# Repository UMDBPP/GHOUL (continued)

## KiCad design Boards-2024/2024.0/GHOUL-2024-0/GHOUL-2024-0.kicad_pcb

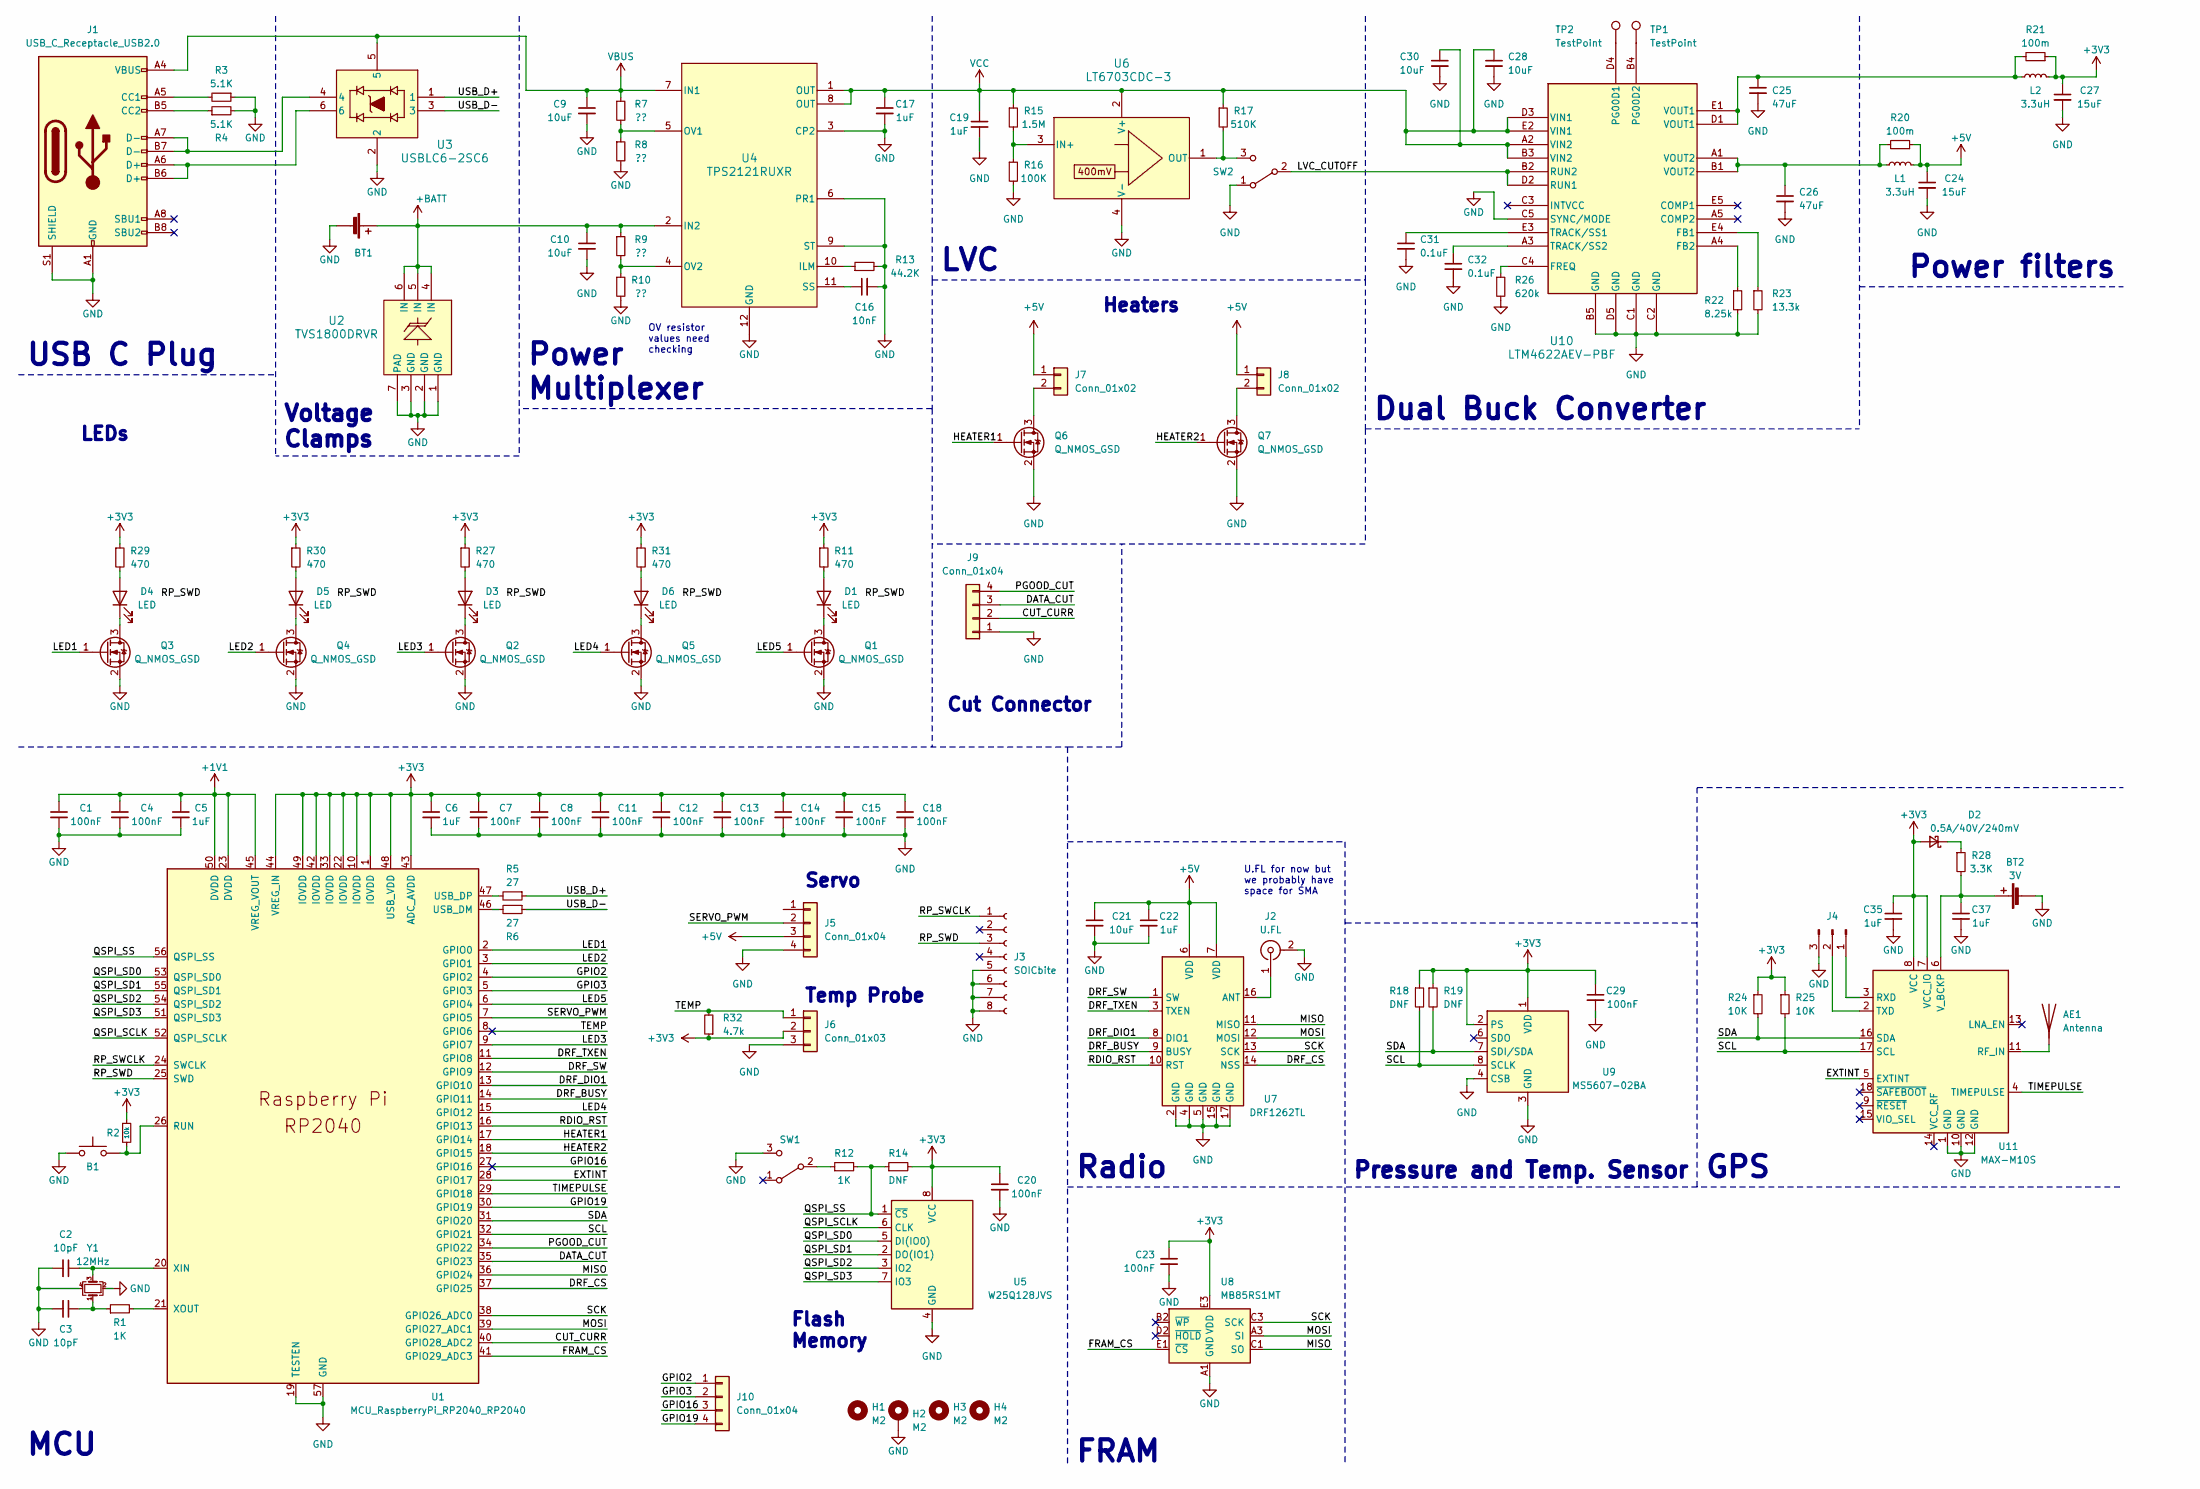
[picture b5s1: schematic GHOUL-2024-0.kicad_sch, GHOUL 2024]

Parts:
AE1: Antenna; ANT_1575AT_JOT-M
B1: KMR2; SW_Push_1P1T_NO_CK_KMR2
BT1: 1S1P LiPo; AMASS_XT30PW-M_1x02_P2.50mm_Horizontal
BT2: 3V; SEIKO_ML414H_IV01E
C1, C4, C7, C8, C11, C12, C13, C14, C15, C18, C20: 100nF; C_0402_1005Metric
C2, C3: 10pF; C_0402_1005Metric
C5, C6, C19: 1uF; C_0402_1005Metric
C9, C10, C21, C28, C30: 10uF; C_0603_1608Metric
C16: 10nF; C_0603_1608Metric
C17, C22, C35, C37: 1uF; C_0603_1608Metric
C23, C29: 100nF; C_0603_1608Metric
C24, C27: 15uF; C_1206_3216Metric
C25, C26: 47uF; C_0805_2012Metric
C31, C32: 0.1uF; C_0603_1608Metric
D1, D3, D4, D5, D6: LED; LED_0603_1608Metric
D2: 0.5A/40V/240mV; D_SOD-123F
H1, H2, H3, H4: M2; MountingHole_2.2mm_M2_Pad
J1: USB_C_Receptacle_USB2.0; USB_C_Receptacle_GCT_USB4105-xx-A_16P_TopMnt_Horizontal
J2: U.FL; U.FL_Molex_MCRF_73412-0110_Vertical
J3: SOICbite; SOIC_clipProgSmall
J4: Conn_01x03_Pin; PinHeader_1x03_P2.54mm_Vertical
J5, J9: Conn_01x04; Molex_SL_171971-0004_1x04_P2.54mm_Vertical
J6: Conn_01x03; Molex_SL_171971-0003_1x03_P2.54mm_Vertical
J7, J8: Conn_01x02; Molex_SL_171971-0002_1x02_P2.54mm_Vertical
J10: Conn_01x04; PinHeader_1x04_P2.54mm_Vertical
L1, L2: 3.3uH; L_1210_3225Metric
Q1, Q2, Q3, Q4, Q5: Q_NMOS_GSD; SOT-23-3
Q6, Q7: Q_NMOS_GSD; SC-59
R1: 1K; C_0402_1005Metric
R2: 10k; R_0603_1608Metric
R3, R4: 5.1K; R_0603_1608Metric_Pad0.98x0.95mm_HandSolder
R5, R6: 27; R_0603_1608Metric
R7, R8, R9, R10: ??; R_0603_1608Metric
R11, R27, R29, R30, R31: 470; R_0603_1608Metric
R12: 1K; R_0603_1608Metric
R13: 44.2K; R_0603_1608Metric
R14, R18, R19: DNF; R_0603_1608Metric
R15: 1.5M; R_0603_1608Metric
R16: 100K; R_0603_1608Metric
R17: 510K; R_0603_1608Metric
R20, R21: 100m; R_0603_1608Metric
R22: 8.25k; R_0603_1608Metric
R23: 13.3k; R_0603_1608Metric
R24, R25: 10K; R_0603_1608Metric
R26: 620k; R_0603_1608Metric
R28: 3.3K; R_0603_1608Metric
R32: 4.7k; R_0603_1608Metric
SW1: CAS-120TB_NDC-M
SW2: SLIDE; CL-SB-12B-01_NDC
TP1, TP2: TestPoint; TestPoint_Keystone_5000-5004_Miniature
U1: MCU_RaspberryPi_RP2040_RP2040; RP2040-QFN-56
U2: TVS1800DRVR; TVS1800
U3: USBLC6-2SC6; SOT-23-6
U4: TPS2121RUXR; TPS2121
U5: W25Q128JVS; W25Q64JVZP
U6: LT6703CDC-3; DFN-3_DC_LIT
U7: DRF1262TL
U8: MB85RS1MT; BGA8CP30X40_5X3_309X228X35B25N
U9: MS5607-02BA; LGA-8_3x5mm_P1.25mm
U10: LTM4622AEV-PBF; LGA25_6P25X6P25_ADI
U11: MAX-M10S; ublox_MAX
Y1: 12MHz; Crystal_SMD_2520-4Pin_2.5x2.0mm

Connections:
+1V1: C1.1, C4.1, C5.1, U1.23 (DVDD), U1.45 (VREG_VOUT), U1.50 (DVDD)
+3V3: C6.1, C7.1, C8.1, C11.1, C12.1, C13.1, C14.1, C15.1, C18.1, C20.1, C23.1, C27.1, C29.1, C35.1, D2.2 (A), J6.2, L2.1, R2.1, R11.1, R14.2, R18.1, R19.1, R21.1, R24.1, R25.1, R27.1, R29.1, R30.1, R31.1, R32.1, U1.1 (IOVDD), U1.10 (IOVDD), U1.22 (IOVDD), U1.33 (IOVDD), U1.42 (IOVDD), U1.43 (ADC_AVDD), U1.44 (VREG_IN), U1.48 (USB_VDD), U1.49 (IOVDD), U5.8 (VCC), U8.E3 (VDD), U9.1 (VDD), U9.2 (PS), U11.7 (VCC_IO), U11.8 (VCC)
+5V: C21.1, C22.1, C24.1, J5.3, J7.1, J8.1, L1.1, R20.1, U7.6 (VDD), U7.7 (VDD)
+BATT: BT1.2 (+), C10.1, R9.1, U2.4 (IN), U2.5 (IN), U2.6 (IN), U4.2 (IN2)
/CUT_CURR: J9.2, U1.40 (GPIO28_ADC2)
/DATA_CUT: J9.3, U1.35 (GPIO23)
/DRF_BUSY: U1.14 (GPIO11), U7.9 (BUSY)
/DRF_CS: U1.37 (GPIO25), U7.14 (NSS)
/DRF_DIO1: U1.13 (GPIO10), U7.8 (DIO1)
/DRF_SW: U1.12 (GPIO9), U7.1 (SW)
/DRF_TXEN: U1.11 (GPIO8), U7.3 (TXEN)
/EXTINT: U1.28 (GPIO17), U11.5 (EXTINT)
/FRAM_CS: U1.41 (GPIO29_ADC3), U8.E1 (~CS)
/GPIO2: J10.1, U1.4 (GPIO2)
/GPIO3: J10.2, U1.5 (GPIO3)
/GPIO16: J10.3, U1.27 (GPIO16)
/GPIO19: J10.4, U1.30 (GPIO19)
/HEATER1: Q6.1 (G), U1.17 (GPIO14)
/HEATER2: Q7.1 (G), U1.18 (GPIO15)
/LED1: Q3.1 (G), U1.2 (GPIO0)
/LED2: Q4.1 (G), U1.3 (GPIO1)
/LED3: Q2.1 (G), U1.9 (GPIO7)
/LED4: Q5.1 (G), U1.15 (GPIO12)
/LED5: Q1.1 (G), U1.6 (GPIO4)
/LVC_CUTOFF: SW2.2 (B), U10.B2 (RUN2), U10.D2 (RUN1)
/MISO: U1.36 (GPIO24), U7.11 (MISO), U8.C1 (SO)
/MOSI: U1.39 (GPIO27_ADC1), U7.12 (MOSI), U8.A3 (SI)
/PGOOD_CUT: J9.4, U1.34 (GPIO22)
/QSPI_SCLK: U1.52 (QSPI_SCLK), U5.6 (CLK)
/QSPI_SD0: U1.53 (QSPI_SD0), U5.5 (DI(IO0))
/QSPI_SD1: U1.55 (QSPI_SD1), U5.2 (DO(IO1))
/QSPI_SD2: U1.54 (QSPI_SD2), U5.3 (IO2)
/QSPI_SD3: U1.51 (QSPI_SD3), U5.7 (IO3)
/QSPI_SS: R12.2, R14.1, U1.56 (QSPI_SS), U5.1 (~CS)
/RDIO_RST: U1.16 (GPIO13), U7.10 (RST)
/RP_SWCLK: J3.1, U1.24 (SWCLK)
/RP_SWD: J3.3, U1.25 (SWD)
/SCK: U1.38 (GPIO26_ADC0), U7.13 (SCK), U8.C3 (SCK)
/SCL: R18.2, R25.2, U1.32 (GPIO21), U9.8 (SCLK), U11.17 (SCL)
/SDA: R19.2, R24.2, U1.31 (GPIO20), U9.7 (SDI/SDA), U11.16 (SDA)
/SERVO_PWM: J5.2, U1.7 (GPIO5)
/TEMP: J6.1, R32.2, U1.8 (GPIO6)
/TIMEPULSE: U1.29 (GPIO18), U11.4 (TIMEPULSE)
/USB_D+: R5.1, U3.1
/USB_D-: R6.1, U3.3
unnamed: AE1.1 (A), U11.11 (RF_IN)
unnamed: BT2.1 (+), C37.1, R28.2, U11.6 (V_BCKP)
unnamed: C3.1, R1.1, Y1.1
unnamed: C25.1, L2.2, R21.2, U10.D1 (VOUT1), U10.E1 (VOUT1)
unnamed: C26.1, L1.2, R20.2, U10.A1 (VOUT2), U10.B1 (VOUT2)
unnamed: D1.2 (A), R11.2
unnamed: D1.1 (K), Q1.3 (D)
unnamed: D2.1 (K), R28.1
unnamed: D3.2 (A), R27.2
unnamed: D3.1 (K), Q2.3 (D)
unnamed: D4.2 (A), R29.2
unnamed: D4.1 (K), Q3.3 (D)
unnamed: D5.2 (A), R30.2
unnamed: D5.1 (K), Q4.3 (D)
unnamed: D6.2 (A), R31.2
unnamed: D6.1 (K), Q5.3 (D)
unnamed: J1.A5 (CC1), R3.2
unnamed: J1.B5 (CC2), R4.1
unnamed: J1.A6 (D+), J1.B6 (D+), U3.6
unnamed: J1.A7 (D-), J1.B7 (D-), U3.4
unnamed: J2.1 (In), U7.16 (ANT)
unnamed: J4.1, U11.3 (RXD)
unnamed: J4.2, U11.2 (TXD)
unnamed: J7.2, Q6.3 (D)
unnamed: J8.2, Q7.3 (D)
unnamed: R12.1, SW1.2 (B)
unnamed: R17.2, SW2.3 (C), U6.1 (OUT)
unnamed: B1.2, R2.2, U1.26 (RUN)
unnamed: R6.2, U1.46 (USB_DM)
unnamed: R5.2, U1.47 (USB_DP)
unnamed: C2.1, U1.20 (XIN), Y1.3
unnamed: R1.2, U1.21 (XOUT)
unnamed: R13.1, U4.10 (ILM)
unnamed: R7.2, R8.1, U4.5 (OV1)
unnamed: R9.2, R10.1, U4.4 (OV2)
unnamed: C16.1, U4.11 (SS)
unnamed: R15.2, R16.1, U6.3 (IN+)
unnamed: R23.1, U10.E4 (FB1)
unnamed: R22.1, U10.A4 (FB2)
unnamed: R26.1, U10.C4 (FREQ)
unnamed: TP2.1, U10.D4 (PG00D1)
unnamed: TP1.1, U10.B4 (PG00D2)
unnamed: C31.1, U10.E3 (TRACK/SS1)
unnamed: C32.1, U10.A3 (TRACK/SS2)
VBUS: C9.1, J1.A4 (VBUS), J1.A9 (VBUS), J1.B4 (VBUS), J1.B9 (VBUS), R7.1, U3.5, U4.7 (IN1)
VCC: C17.1, C19.1, C28.1, C30.1, R15.1, R17.1, U4.1 (OUT), U4.8 (OUT), U6.2 (V+), U10.A2 (VIN2), U10.B3 (VIN2), U10.D3 (VIN1), U10.E2 (VIN1)

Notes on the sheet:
MCU
Voltage Clamps
LEDs
Heaters
Temp Probe
Dual Buck Converter
Flash Memory
FRAM
Servo
Cut Connector
Power filters
USB C Plug
U.FL for now but we probably have space for SMA
Pressure and Temp. Sensor
Radio
OV resistor values need checking
GPS
LVC
Power Multiplexer

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
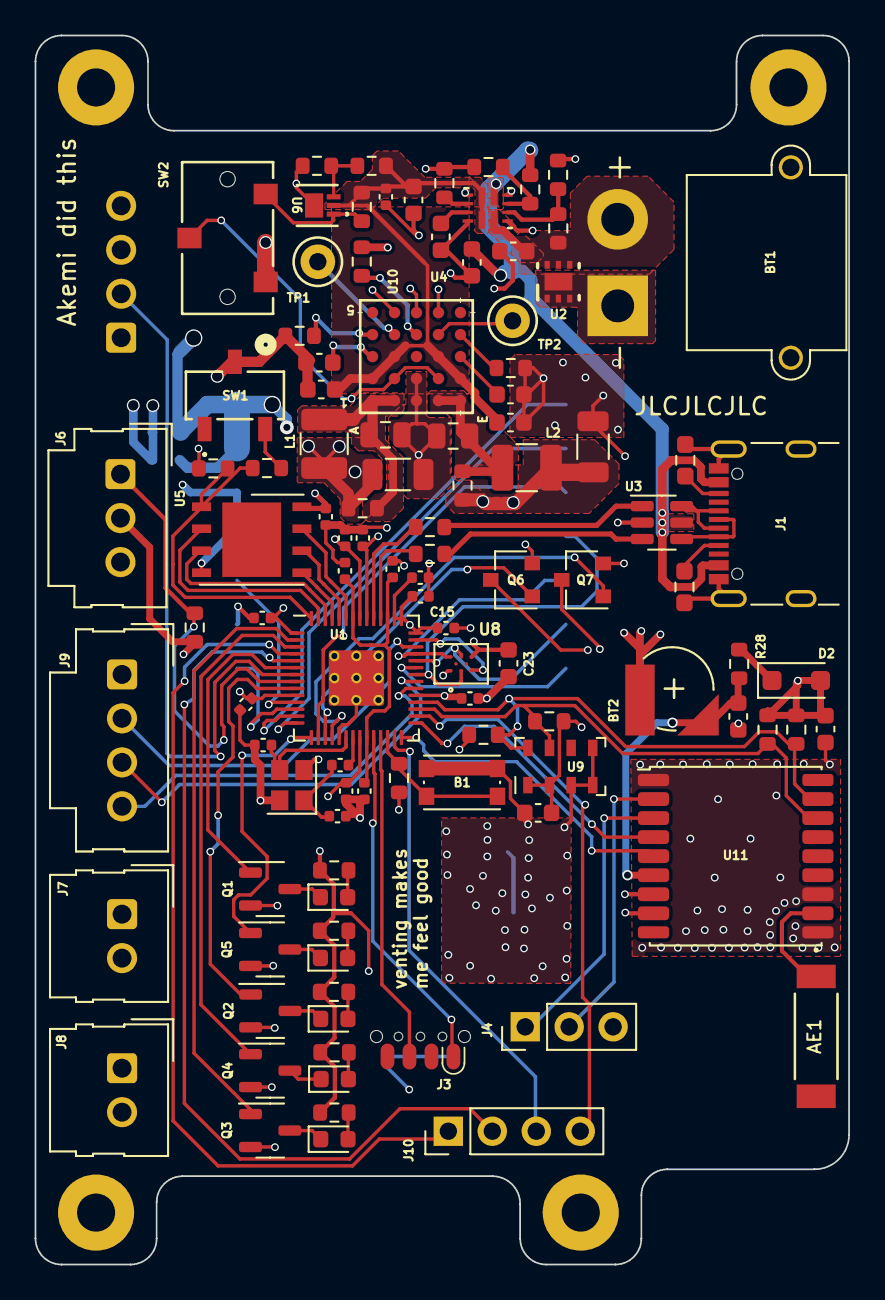
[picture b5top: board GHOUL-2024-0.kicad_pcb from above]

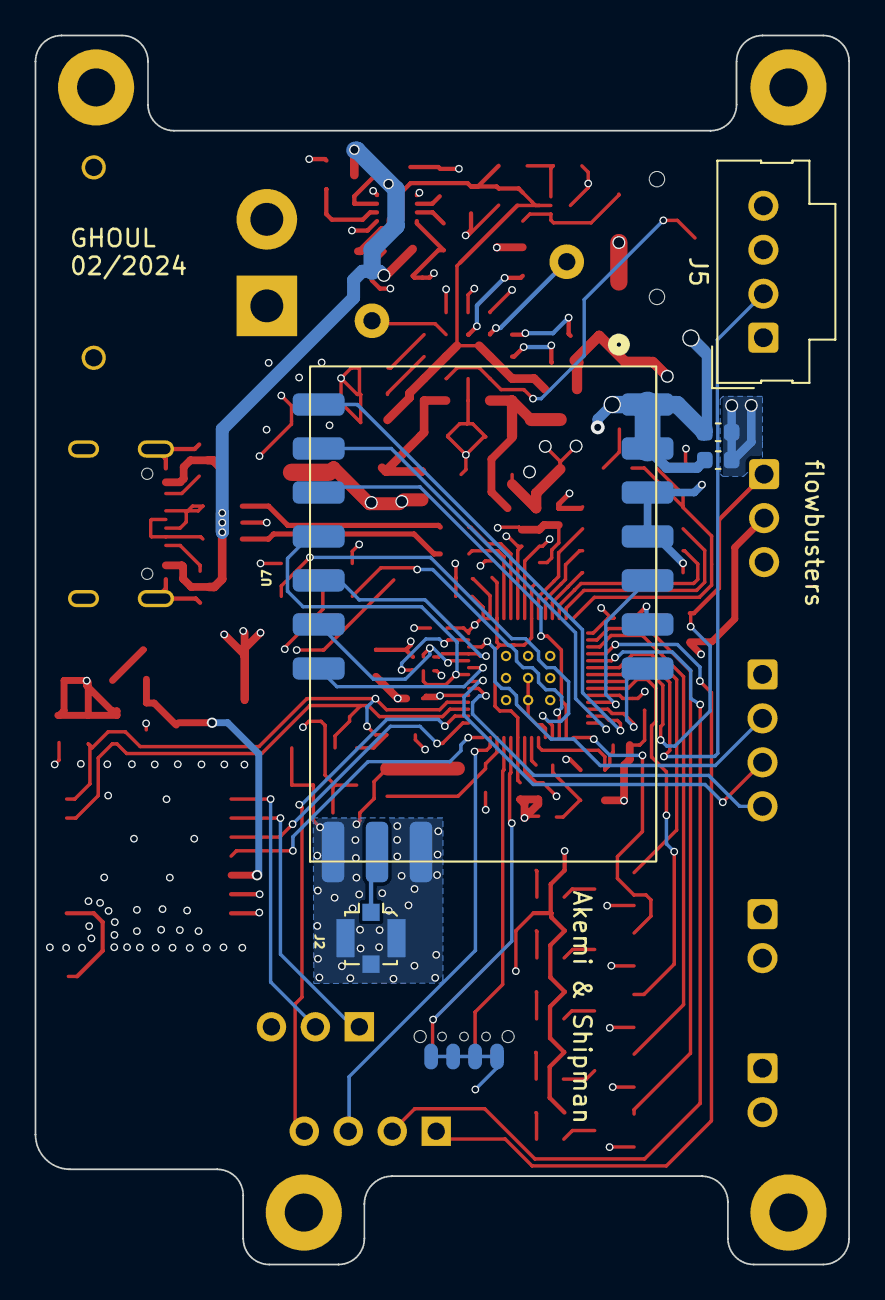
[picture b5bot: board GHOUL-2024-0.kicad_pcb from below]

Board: 4 copper layers, 47.0 x 71.0 mm, 115 parts (5 on the bottom side), 92 nets.

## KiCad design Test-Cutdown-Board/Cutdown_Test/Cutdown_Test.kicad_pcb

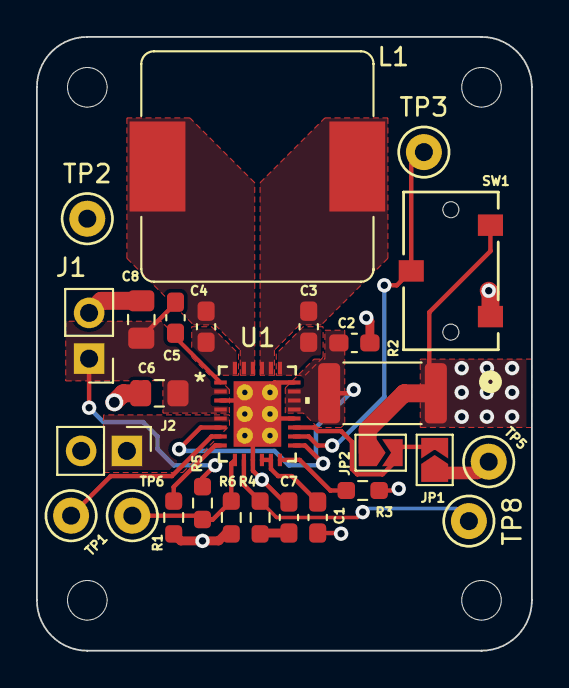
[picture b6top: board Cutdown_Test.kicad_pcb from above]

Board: 4 copper layers, 27.5 x 34.1 mm, 31 parts (0 on the bottom side), 19 nets.

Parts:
C1: 4.7uF; C_0603_1608Metric_Pad1.08x0.95mm_HandSolder
C2: 10uF; C_0603_1608Metric_Pad1.08x0.95mm_HandSolder
C3, C4: 220nF; C_0603_1608Metric_Pad1.08x0.95mm_HandSolder
C5: 22nF; C_0603_1608Metric_Pad1.08x0.95mm_HandSolder
C6, C8: 22uF; C_0805_2012Metric_Pad1.18x1.45mm_HandSolder
C7: 680p; C_0603_1608Metric_Pad1.08x0.95mm_HandSolder
H1, H2, H3, H4: M2; MountingHole_2.2mm_M2
J1: Nichrome; PinHeader_1x02_P2.54mm_Vertical
J2: Conn_01x02_Socket; PinHeader_1x02_P2.54mm_Vertical
JP1, JP2: SolderJumper_2_Open; SolderJumper-2_P1.3mm_Open_TrianglePad1.0x1.5mm
L1: 3.3uH; L_Bourns_SRP1265A
R1: 81.1k; R_0603_1608Metric_Pad0.98x0.95mm_HandSolder
R2: 5m; R_2512_6332Metric
R3: 75k; R_0603_1608Metric_Pad0.98x0.95mm_HandSolder
R4: 56.2k; R_0603_1608Metric_Pad0.98x0.95mm_HandSolder
R5, R6: 154k; R_0603_1608Metric_Pad0.98x0.95mm_HandSolder
SW1: SW_SPDT; CL-SB-12B-01_NDC
TP1, TP2, TP3, TP5, TP6, TP8: TestPoint; TestPoint_Keystone_5000-5004_Miniature
U1: LT3120JV-PBF; LQFN28_Rev0_ADI-M

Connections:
+3V3: JP1.1 (A), TP5.1
+BATT: J2.1, JP2.1 (A), R2.1, SW1.3 (C), U1.5 (ISP)
/EN: SW1.2 (B), TP3.1, U1.16 (EN/UVLO)
/POWR_OUT: C5.2, C6.1, C8.1, J1.1, R5.1, U1.2 (PVOUT), U1.4 (PVOUT)
GND: C1.2, C2.2, C6.2, C7.2, C8.2, J1.2, J2.2, R1.2, R3.2, R6.2, SW1.1 (A), TP2.1, U1.3 (GND), U1.11 (GND), U1.18 (GND), U1.22 (GND), U1.29 (PGND)
unnamed: C3.2, L1.1, U1.24 (SW1), U1.25 (SW1)
unnamed: C4.2, L1.2, U1.26 (SW2), U1.27 (SW2)
unnamed: C7.1, R4.2
unnamed: JP1.2 (B), JP2.2 (B), U1.17 (VIN)
unnamed: C3.1, U1.23 (BST1)
unnamed: C4.1, U1.28 (BST2)
unnamed: C5.1, U1.1 (BST3)
unnamed: R5.2, R6.1, TP6.1, U1.9 (FB)
unnamed: C2.1, R2.2, U1.6 (ISN), U1.15 (SYNC/MODE), U1.19 (PVIN), U1.20 (PVIN), U1.21 (PVIN)
unnamed: C1.1, U1.12 (MPCC), U1.13 (VCC)
unnamed: TP1.1, U1.7 (PGOOD)
unnamed: R1.1, U1.8 (PROG)
unnamed: R3.1, U1.14 (RT)
unnamed: R4.1, TP8.1, U1.10 (VC)

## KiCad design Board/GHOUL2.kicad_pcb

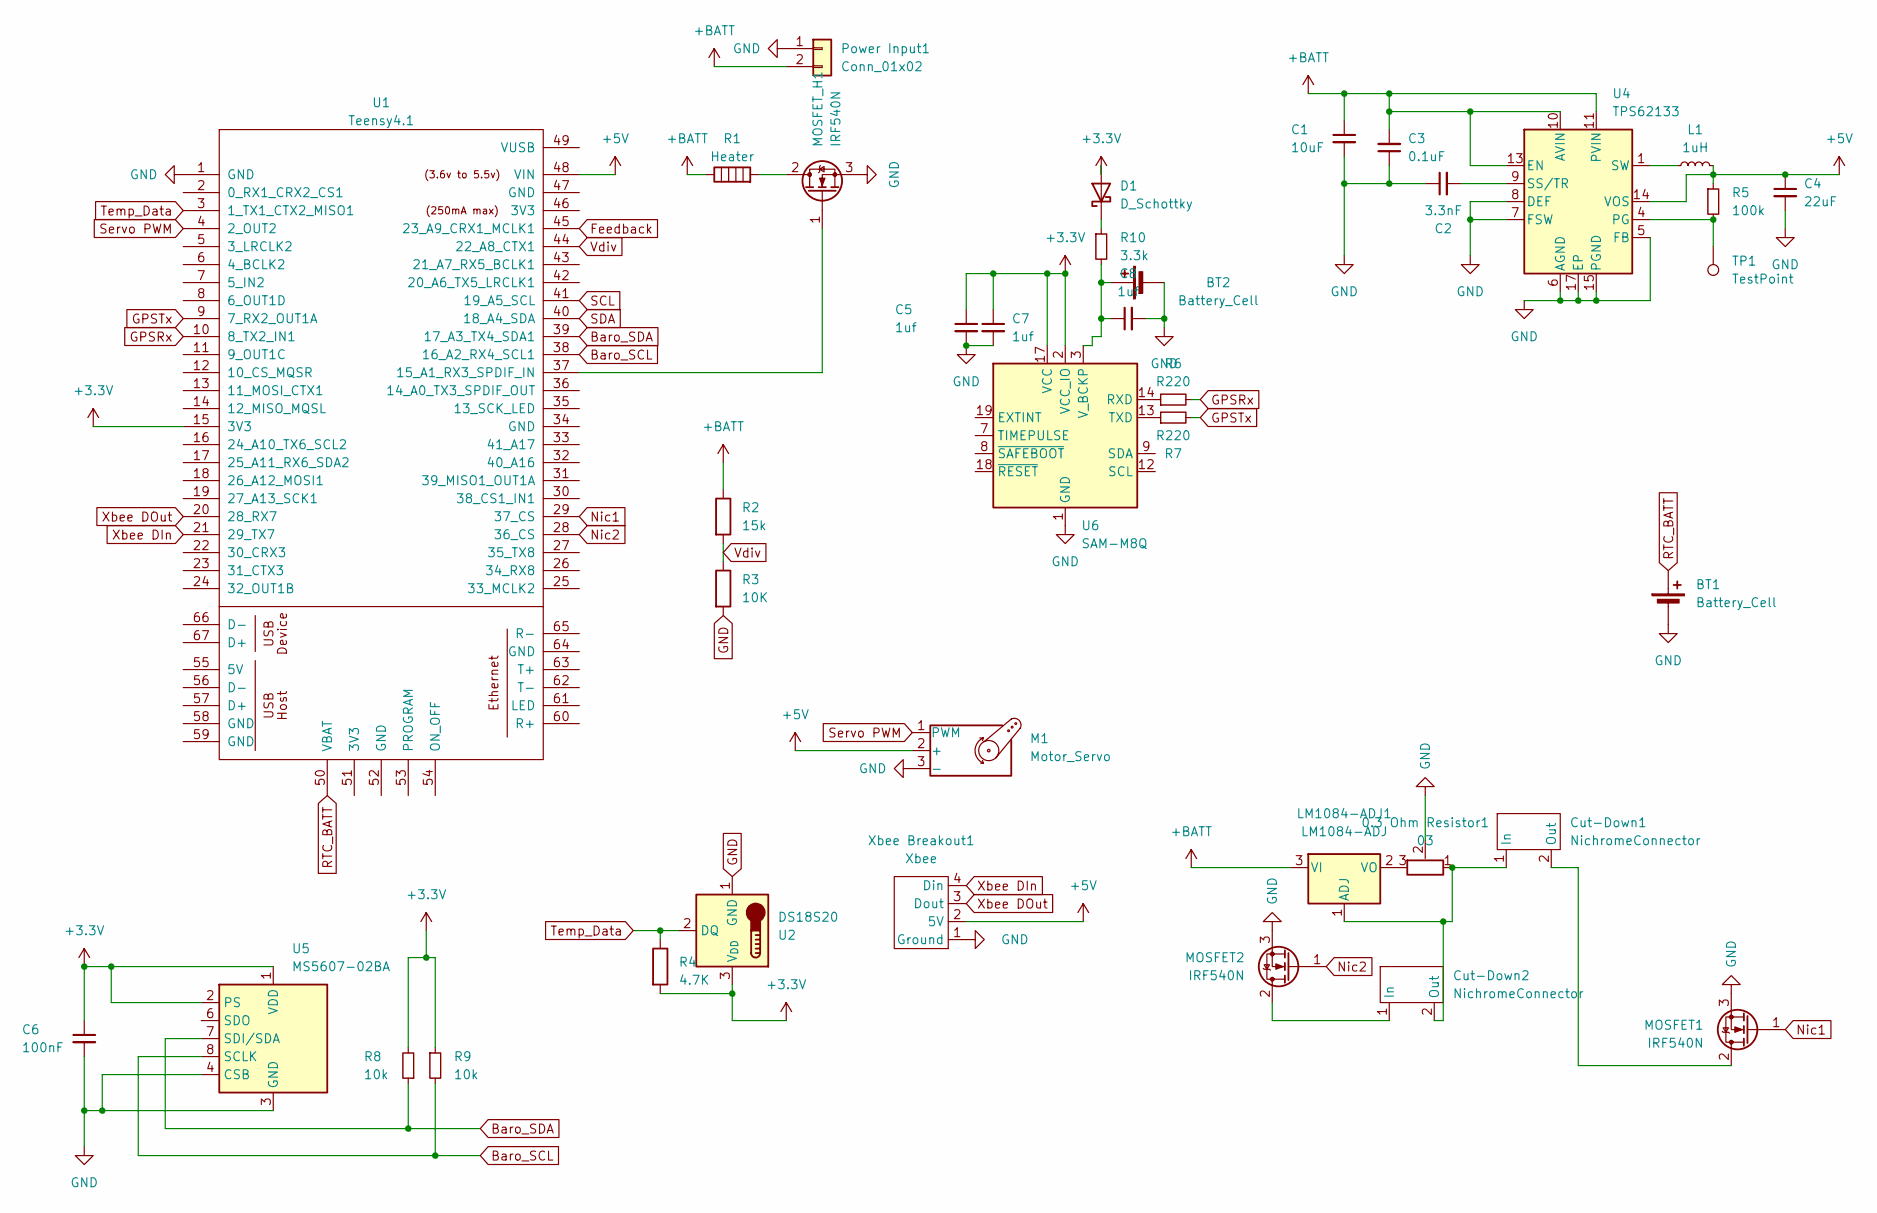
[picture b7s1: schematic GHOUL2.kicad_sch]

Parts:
0.3 Ohm Resistor1: 03; TO-263-2
BT1: Battery_Cell; BatteryHolder_Keystone_3000_1x12mm
BT2: Battery_Cell; SEIKO_ML414H_IV01E
C1: 10uF; C_0603_1608Metric_Pad1.08x0.95mm_HandSolder
C2: 3.3nF; C_0603_1608Metric_Pad1.08x0.95mm_HandSolder
C3: 0.1uF; C_0603_1608Metric_Pad1.08x0.95mm_HandSolder
C4: 22uF; C_0603_1608Metric_Pad1.08x0.95mm_HandSolder
C5, C7, C8: 1uf; C_0201_0603Metric_Pad0.64x0.40mm_HandSolder
C6: 100nF; C_0603_1608Metric_Pad1.08x0.95mm_HandSolder
Cut-Down1, Cut-Down2: NichromeConnector; JST_EH_B2B-EH-A_1x02_P2.50mm_Vertical
D1: D_Schottky; D_SOD-123F
L1: 1uH; L_Coilcraft_XxL4040
LM1084-ADJ1: LM1084-ADJ; TO-263-3_TabPin2
M1: Motor_Servo; JST_XH_B3B-XH-A_1x03_P2.50mm_Vertical
MOSFET1, MOSFET2: IRF540N; TO-252-2
MOSFET_H1: IRF540N; TO-252-2
Power Input1: Conn_01x02; AMASS_XT30PW-M_1x02_P2.50mm_Horizontal
R1: Heater; JST_EH_B2B-EH-A_1x02_P2.50mm_Vertical
R2: 15k; R_Axial_DIN0204_L3.6mm_D1.6mm_P7.62mm_Horizontal
R3: 10K; R_Axial_DIN0204_L3.6mm_D1.6mm_P7.62mm_Horizontal
R4: 4.7K; R_Axial_DIN0204_L3.6mm_D1.6mm_P7.62mm_Horizontal
R5: 100k; R_0603_1608Metric_Pad0.98x0.95mm_HandSolder
R6, R7: R220; R_0201_0603Metric_Pad0.64x0.40mm_HandSolder
R8, R9: 10k; R_0603_1608Metric_Pad0.98x0.95mm_HandSolder
R10: 3.3k; R_0201_0603Metric_Pad0.64x0.40mm_HandSolder
TP1: TestPoint; TestPoint_Keystone_5000-5004_Miniature
U1: Teensy4.1; Teensy41
U2: DS18S20; JST_EH_B3B-EH-A_1x03_P2.50mm_Vertical
U4: TPS62133; VQFN-16-1EP_3x3mm_P0.5mm_EP1.68x1.68mm_ThermalVias
U5: MS5607-02BA; LGA-8_3x5mm_P1.25mm
U6: SAM-M8Q; ublox_SAM-M8Q
Xbee Breakout1: Xbee; XBee Explorer

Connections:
+3.3V: C5.1, C6.1, C7.1, D1.2 (A), R4.2, R8.2, R9.1, U1.15 (3V3), U2.3 (V_{DD}), U5.1 (VDD), U5.2 (PS), U6.2 (VCC_IO), U6.17 (VCC)
+5V: C4.1, L1.2, M1.2 (+), R5.1, U1.48 (VIN), U4.14 (VOS), Xbee Breakout1.2 (5V)
+BATT: C1.1, C3.2, LM1084-ADJ1.3 (VI), Power Input1.2, R1.1, R2.1, U4.10 (AVIN), U4.11 (PVIN), U4.12 (PVIN), U4.13 (EN)
Baro_SCL: R9.2, U1.38 (16_A2_RX4_SCL1), U5.8 (SCLK)
Baro_SDA: R8.1, U1.39 (17_A3_TX4_SDA1), U5.7 (SDI/SDA)
Feedback: U1.45 (23_A9_CRX1_MCLK1)
GND: 0.3 Ohm Resistor1.2, BT1.2 (-), BT2.2 (-), C1.2, C2.1, C3.1, C4.2, C5.2, C6.2, C7.2, C8.2, M1.3 (-), MOSFET1.3 (S), MOSFET2.3 (S), MOSFET_H1.3 (S), Power Input1.1, R3.2, U1.1 (GND), U2.1 (GND), U4.5 (FB), U4.6 (AGND), U4.7 (FSW), U4.8 (DEF), U4.15 (PGND), U4.16 (PGND), U4.17 (EP), U5.3 (GND), U5.4 (CSB), U5.5 (CSB), U6.1 (GND), U6.4 (GND), U6.5 (GND), U6.6 (GND), U6.10 (GND), U6.11 (GND), U6.15 (GND), U6.16 (GND), U6.20 (GND), Xbee Breakout1.1 (Ground)
GPSRx: R6.2, U1.10 (8_TX2_IN1)
GPSTx: R7.2, U1.9 (7_RX2_OUT1A)
unnamed: BT2.1 (+), C8.1, R10.2, U6.3 (V_BCKP)
unnamed: 0.3 Ohm Resistor1.1, Cut-Down1.1 (In), Cut-Down2.2 (Out), LM1084-ADJ1.1 (ADJ)
unnamed: Cut-Down1.2 (Out), MOSFET1.2 (D)
unnamed: Cut-Down2.1 (In), MOSFET2.2 (D)
unnamed: D1.1 (K), R10.1
unnamed: L1.1, U4.1 (SW), U4.2 (SW), U4.3 (SW)
unnamed: 0.3 Ohm Resistor1.3, LM1084-ADJ1.2 (VO)
unnamed: MOSFET_H1.2 (D), R1.2
unnamed: MOSFET_H1.1 (G), U1.37 (15_A1_RX3_SPDIF_IN)
unnamed: R5.2, TP1.1, U4.4 (PG)
unnamed: C2.2, U4.9 (SS/TR)
unnamed: R6.1, U6.14 (RXD)
unnamed: R7.1, U6.13 (TXD)
Nic1: MOSFET1.1 (G), U1.29 (37_CS)
Nic2: MOSFET2.1 (G), U1.28 (36_CS)
RTC_BATT: BT1.1 (+), U1.50 (VBAT)
SCL: U1.41 (19_A5_SCL)
SDA: U1.40 (18_A4_SDA)
Servo PWM: M1.1 (PWM), U1.4 (2_OUT2)
Temp_Data: R4.1, U1.3 (1_TX1_CTX2_MISO1), U2.2 (DQ)
Vdiv: R2.2, R3.1, U1.44 (22_A8_CTX1)
Xbee DIn: U1.21 (29_TX7), Xbee Breakout1.4 (Din)
Xbee DOut: U1.20 (28_RX7), Xbee Breakout1.3 (Dout)

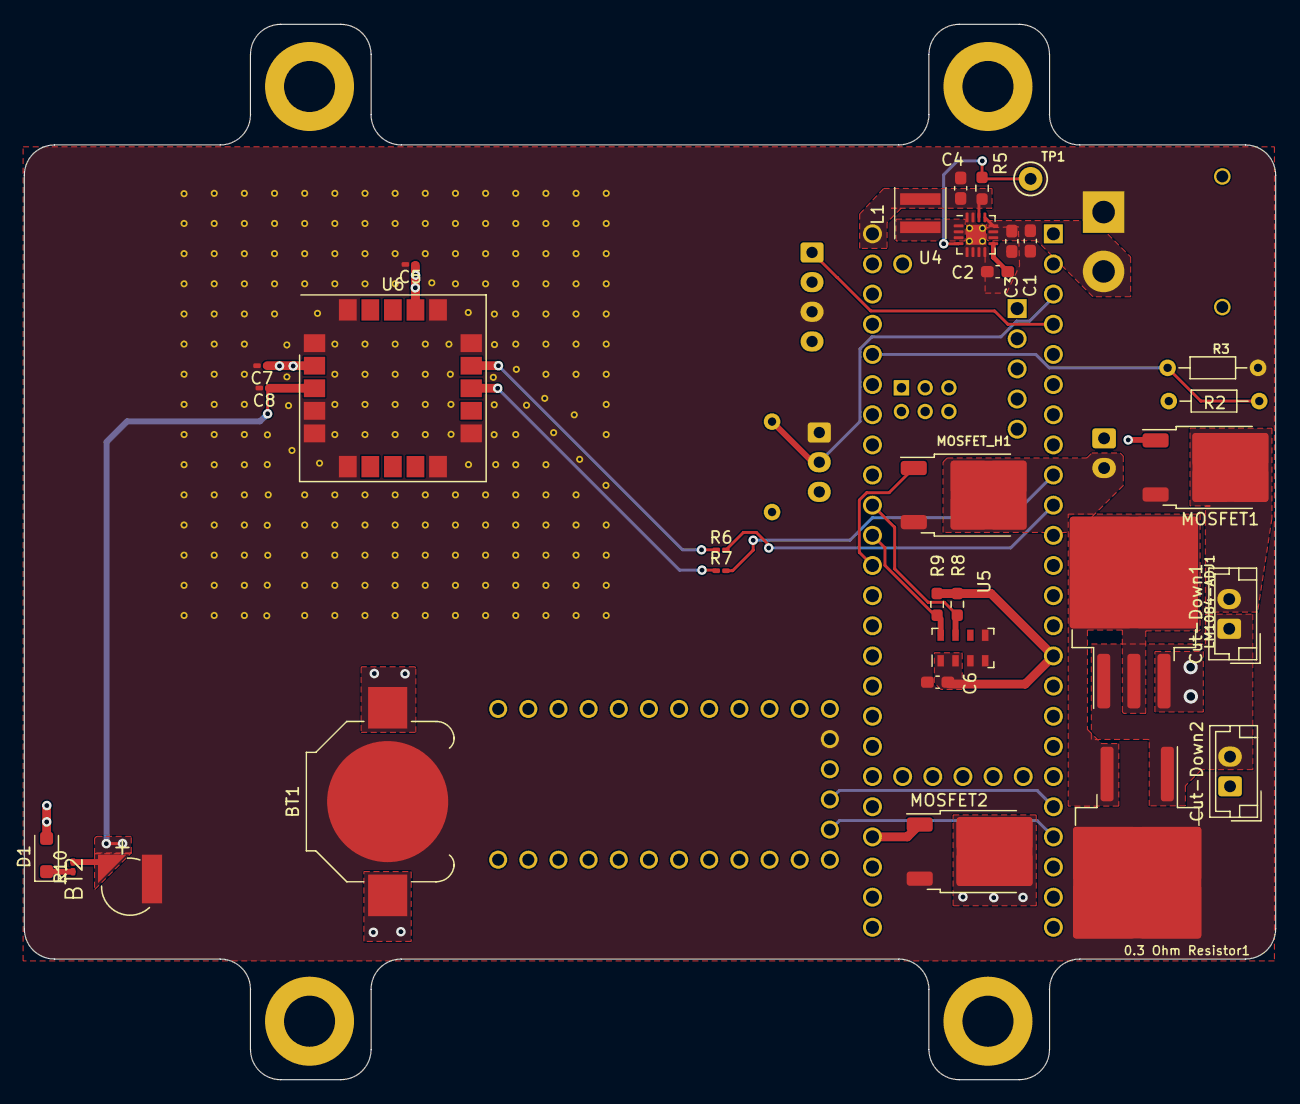
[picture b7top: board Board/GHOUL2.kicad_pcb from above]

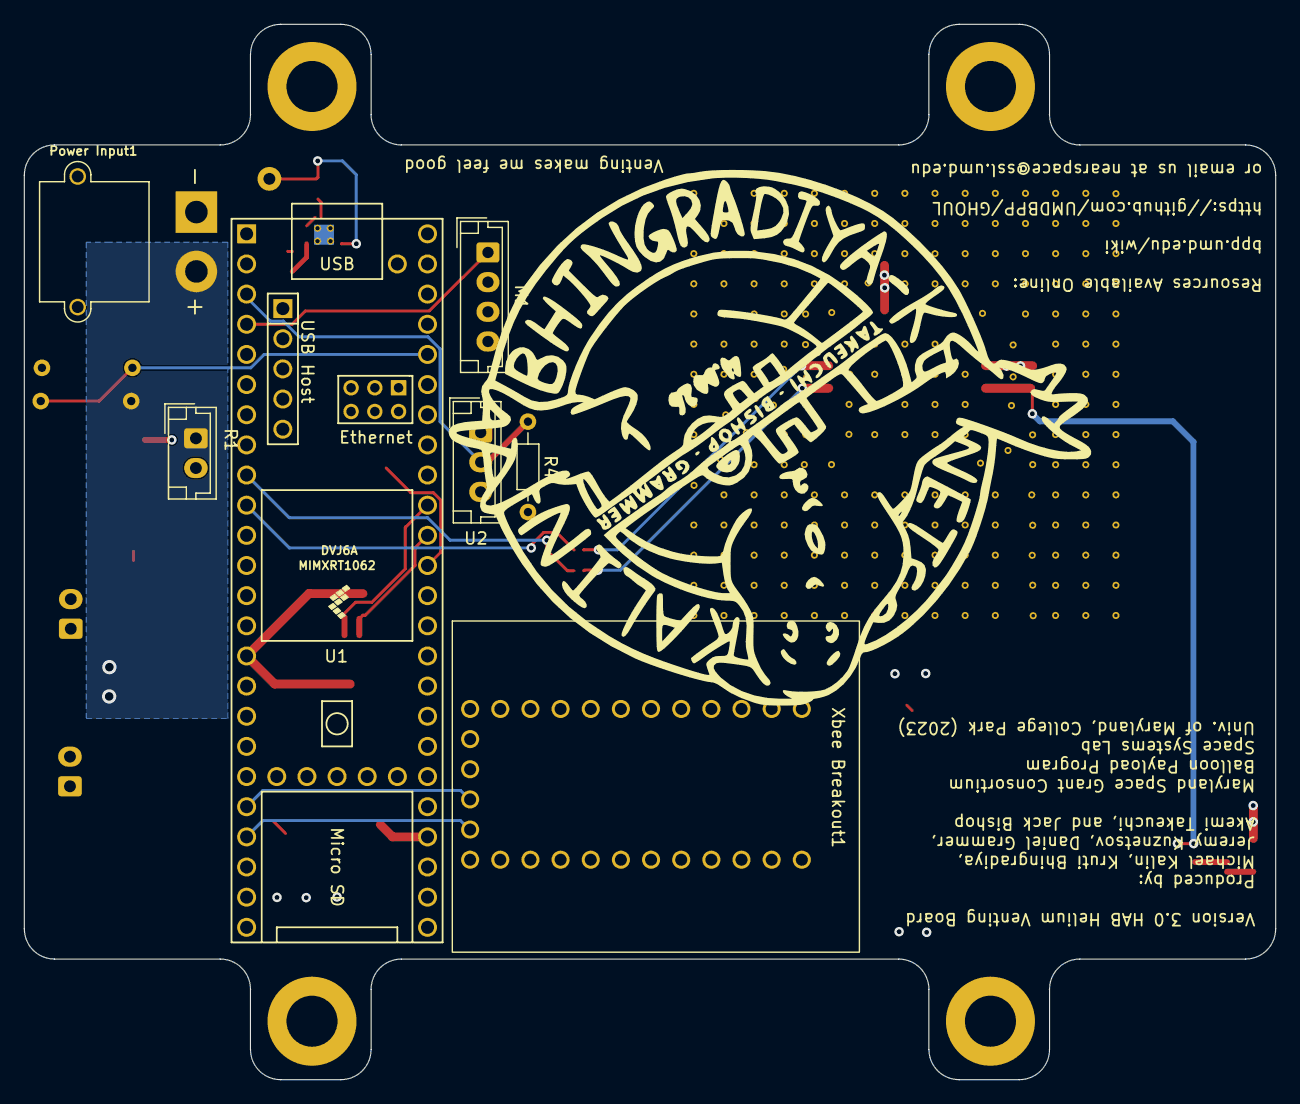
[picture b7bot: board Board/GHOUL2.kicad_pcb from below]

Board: 4 copper layers, 105.4 x 88.9 mm, 38 parts (7 on the bottom side), 29 nets.

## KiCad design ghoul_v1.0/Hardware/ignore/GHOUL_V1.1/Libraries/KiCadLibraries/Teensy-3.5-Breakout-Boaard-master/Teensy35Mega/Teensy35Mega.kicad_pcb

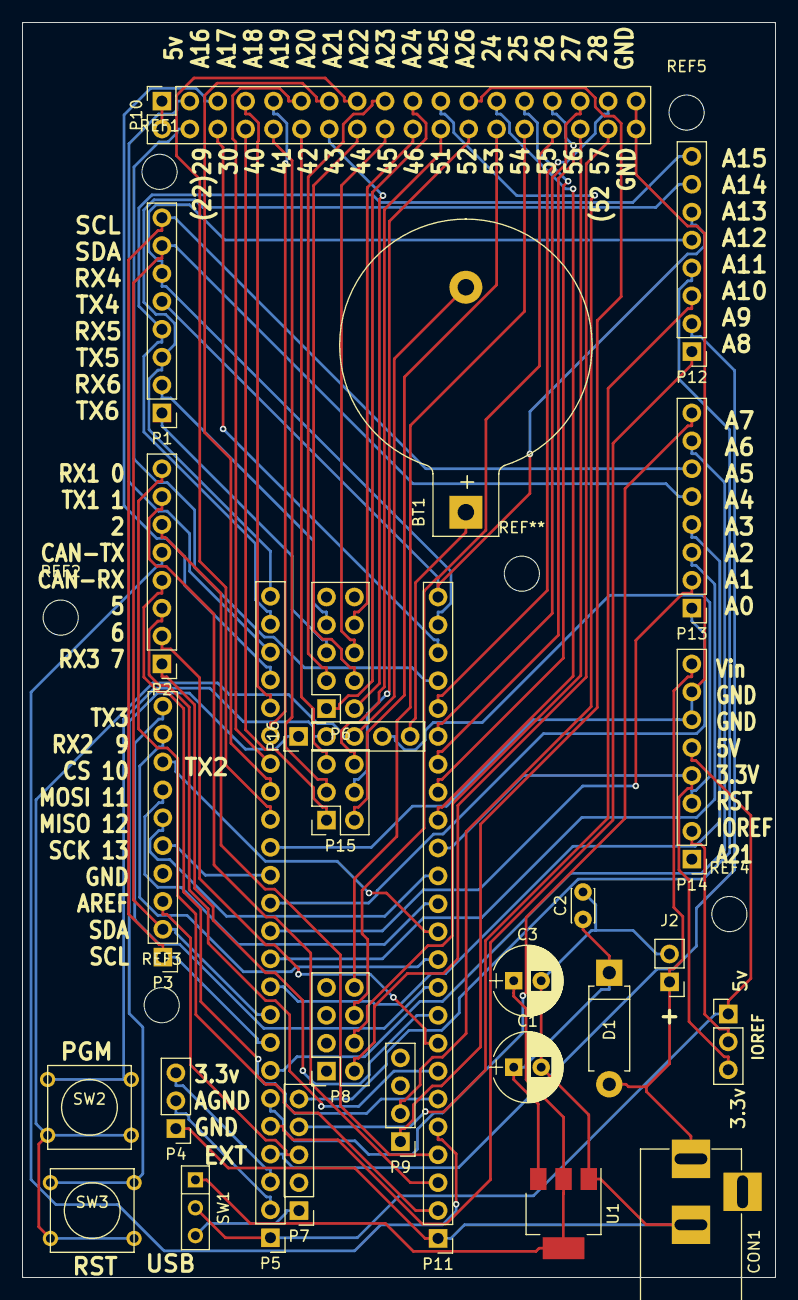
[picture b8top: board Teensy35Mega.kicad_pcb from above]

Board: 2 copper layers, 68.6 x 114.3 mm, 33 parts (0 on the bottom side), 82 nets.

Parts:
BT1: BATTERY; Keystone_103_1x20mm-CoinCell
C1, C3: CP; CP_Radial_D6.3mm_P2.50mm
C2: C; C_Disc_D3.0mm_W2.0mm_P2.50mm
CON1: BARREL_JACK
D1: D_Small; D_DO-15_P10.16mm_Horizontal
J1: CONN_01X03; Pin_Header_Straight_1x03_Pitch2.54mm
J2: CONN_01X02; Pin_Header_Straight_1x02_Pitch2.54mm
P1, P2, P12, P13, P14: CONN_01X08; Socket_Strip_Straight_1x08_Pitch2.54mm
P3: CONN_01X10; Socket_Strip_Straight_1x10_Pitch2.54mm
P4: CONN_01X03; Pin_Header_Straight_1x03_Pitch2.54mm
P5, P11: CONN_01X24; Socket_Strip_Straight_1x24_Pitch2.54mm
P6: CONN_02X05; Socket_Strip_Straight_2x05_Pitch2.54mm
P7, P16: CONN_01X05; Socket_Strip_Straight_1x05_Pitch2.54mm
P8: CONN_02X04; Socket_Strip_Straight_2x04_Pitch2.54mm
P9: CONN_01X04; Socket_Strip_Straight_1x04_Pitch2.54mm
P10: CONN_02X18; Socket_Strip_Straight_2x18_Pitch2.54mm
P15: CONN_02X03; Socket_Strip_Straight_2x03_Pitch2.54mm
REF1, REF2, REF3, REF4, REF5: MountingHole_3.2mm_M3_ISO14580_Pad; MountingHole_3.2mm_M3
SW1: PWR SEL; SW_Micro_SPST
SW2: PGM; SW_PUSH_SMALL
SW3: RST; SW_PUSH_SMALL
U1: NCP1117ST50T3G_MountingTab; SOT-223

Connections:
unnamed: BT1.1, P16.5
unnamed: BT1.2, P16.3, SW2.2, SW3.2
unnamed: C1.1, C2.1, D1.1, U1.3
unnamed: C1.2, C2.2, C3.2, CON1.2, J2.2, P4.1, P11.1, U1.1
unnamed: C3.1, SW1.1, U1.2, U1.4
unnamed: CON1.1, D1.2, J2.1, P14.8
unnamed: J1.1, P5.1, P14.5, SW1.2
unnamed: J1.2, P14.2
unnamed: J1.3, P11.15, P14.4
unnamed: P1.1, P6.5
unnamed: P1.2, P6.7
unnamed: P1.3, P5.24, P12.7
unnamed: P1.4, P5.23, P12.8
unnamed: P1.5, P11.24, P12.6
unnamed: P1.6, P11.23, P12.5
unnamed: P1.7, P3.2, P5.9, P13.5
unnamed: P1.8, P3.1, P5.8, P13.6
unnamed: P3.3, P7.3
unnamed: P3.5, P5.14
unnamed: P4.2, P5.2
unnamed: P4.3, P5.3
unnamed: P7.1, SW1.3
unnamed: P10.1, P10.2
unnamed: P5.22, P10.3
unnamed: P10.4, P11.21
unnamed: P5.21, P10.5
unnamed: P10.6, P11.22
unnamed: P5.20, P10.7
unnamed: P10.8, P15.1
unnamed: P5.19, P10.9
unnamed: P10.10, P15.3
unnamed: P5.18, P10.11
unnamed: P10.12, P15.5
unnamed: P5.17, P10.13
unnamed: P6.2, P10.14
unnamed: P5.16, P10.15
unnamed: P6.4, P10.16
unnamed: P6.3, P10.17
unnamed: P6.6, P10.18
unnamed: P6.1, P10.19
unnamed: P6.8, P10.20
unnamed: P9.2, P10.21
unnamed: P10.22, P15.6
unnamed: P9.1, P10.23
unnamed: P10.24, P15.4
unnamed: P10.25, P11.16
unnamed: P10.26, P15.2
unnamed: P10.27, P11.17
unnamed: P8.8, P10.28
unnamed: P10.29, P11.18
unnamed: P8.6, P10.30
unnamed: P10.31, P11.19
unnamed: P8.4, P10.32
unnamed: P10.33, P11.20
unnamed: P8.2, P10.34
unnamed: P5.15, P10.35, P10.36, P14.6, P14.7
unnamed: P2.8, P11.2
unnamed: P2.7, P11.3
unnamed: P2.6, P11.4
unnamed: P2.5, P11.5
unnamed: P2.4, P11.6
unnamed: P2.3, P11.7
unnamed: P2.2, P11.8
unnamed: P2.1, P11.9
unnamed: P3.10, P11.10
unnamed: P3.9, P11.11
unnamed: P3.8, P11.12
unnamed: P3.7, P11.13
unnamed: P3.6, P11.14
unnamed: P5.5, P12.1
unnamed: P5.4, P12.2
unnamed: P7.4, P12.3
unnamed: P7.5, P12.4
unnamed: P5.13, P13.1
unnamed: P5.12, P13.2
unnamed: P5.11, P13.3
unnamed: P5.10, P13.4
unnamed: P5.7, P13.7
unnamed: P5.6, P13.8
unnamed: P14.3, P16.4
unnamed: P16.1, SW3.1
unnamed: P16.2, SW2.1

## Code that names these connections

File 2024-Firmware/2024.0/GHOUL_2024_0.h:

#ifndef _BITSv5_H
#define _BITSv5_H

#define SCK_PIN 26
#define MOSI_PIN 27
#define MISO_PIN 24

#define RADIO_CS 25

#define TXEN_PIN 8
#define DIO1_PIN 10
#define BUSY_PIN 11
#define SW_PIN 9
#define RADIO_RST 13

#define SDA_PIN 20
#define SCL_PIN 21

#define GPS_ADDR 0x42
#define EXTINT_PIN 17
#define TIMEPULSE_PIN 18

#define FRAM_CS 29

#define LED1_PIN 0
#define LED2_PIN 1
#define LED3_PIN 7
#define LED4_PIN 12
#define LED5_PIN 4

#define GPIO2_PIN 2
#define GPIO3_PIN 3
#define GPIO16_PIN 16
#define GPIO19_PIN 19

#define SERVO_PWM 5

#define TEMP_PIN 6

#define HEATER1_PIN 14
#define HEATER2_PIN 14

#define PGOOD_CUT_PIN 22
#define DATA_CUT 23
#define CURRENT_CUT 28

#define LOG_INIT_ADDR 8192
#define LOG_MAX_ADDR 131072

#define INCLUDE_DEBUG \
    1  // controls if debug conditionals are included at compile time

extern short debug_msgs;  // controls if debug messages are printed

#endif
